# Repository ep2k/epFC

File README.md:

# epFC - Famicom Emulator on an FPGA

epFC is an implementation of Nintendo's __Family Computer__ (__Nintendo Entertainment System__) written in SystemVerilog.
It works on an FPGA board with a board for connection to Famicom cartridges.

It has no built-in mappers except for NROM, and can basically only operate in real-time communication with cartridges.

The operation has been confirmed with Terasic DE0-CV Board.

")

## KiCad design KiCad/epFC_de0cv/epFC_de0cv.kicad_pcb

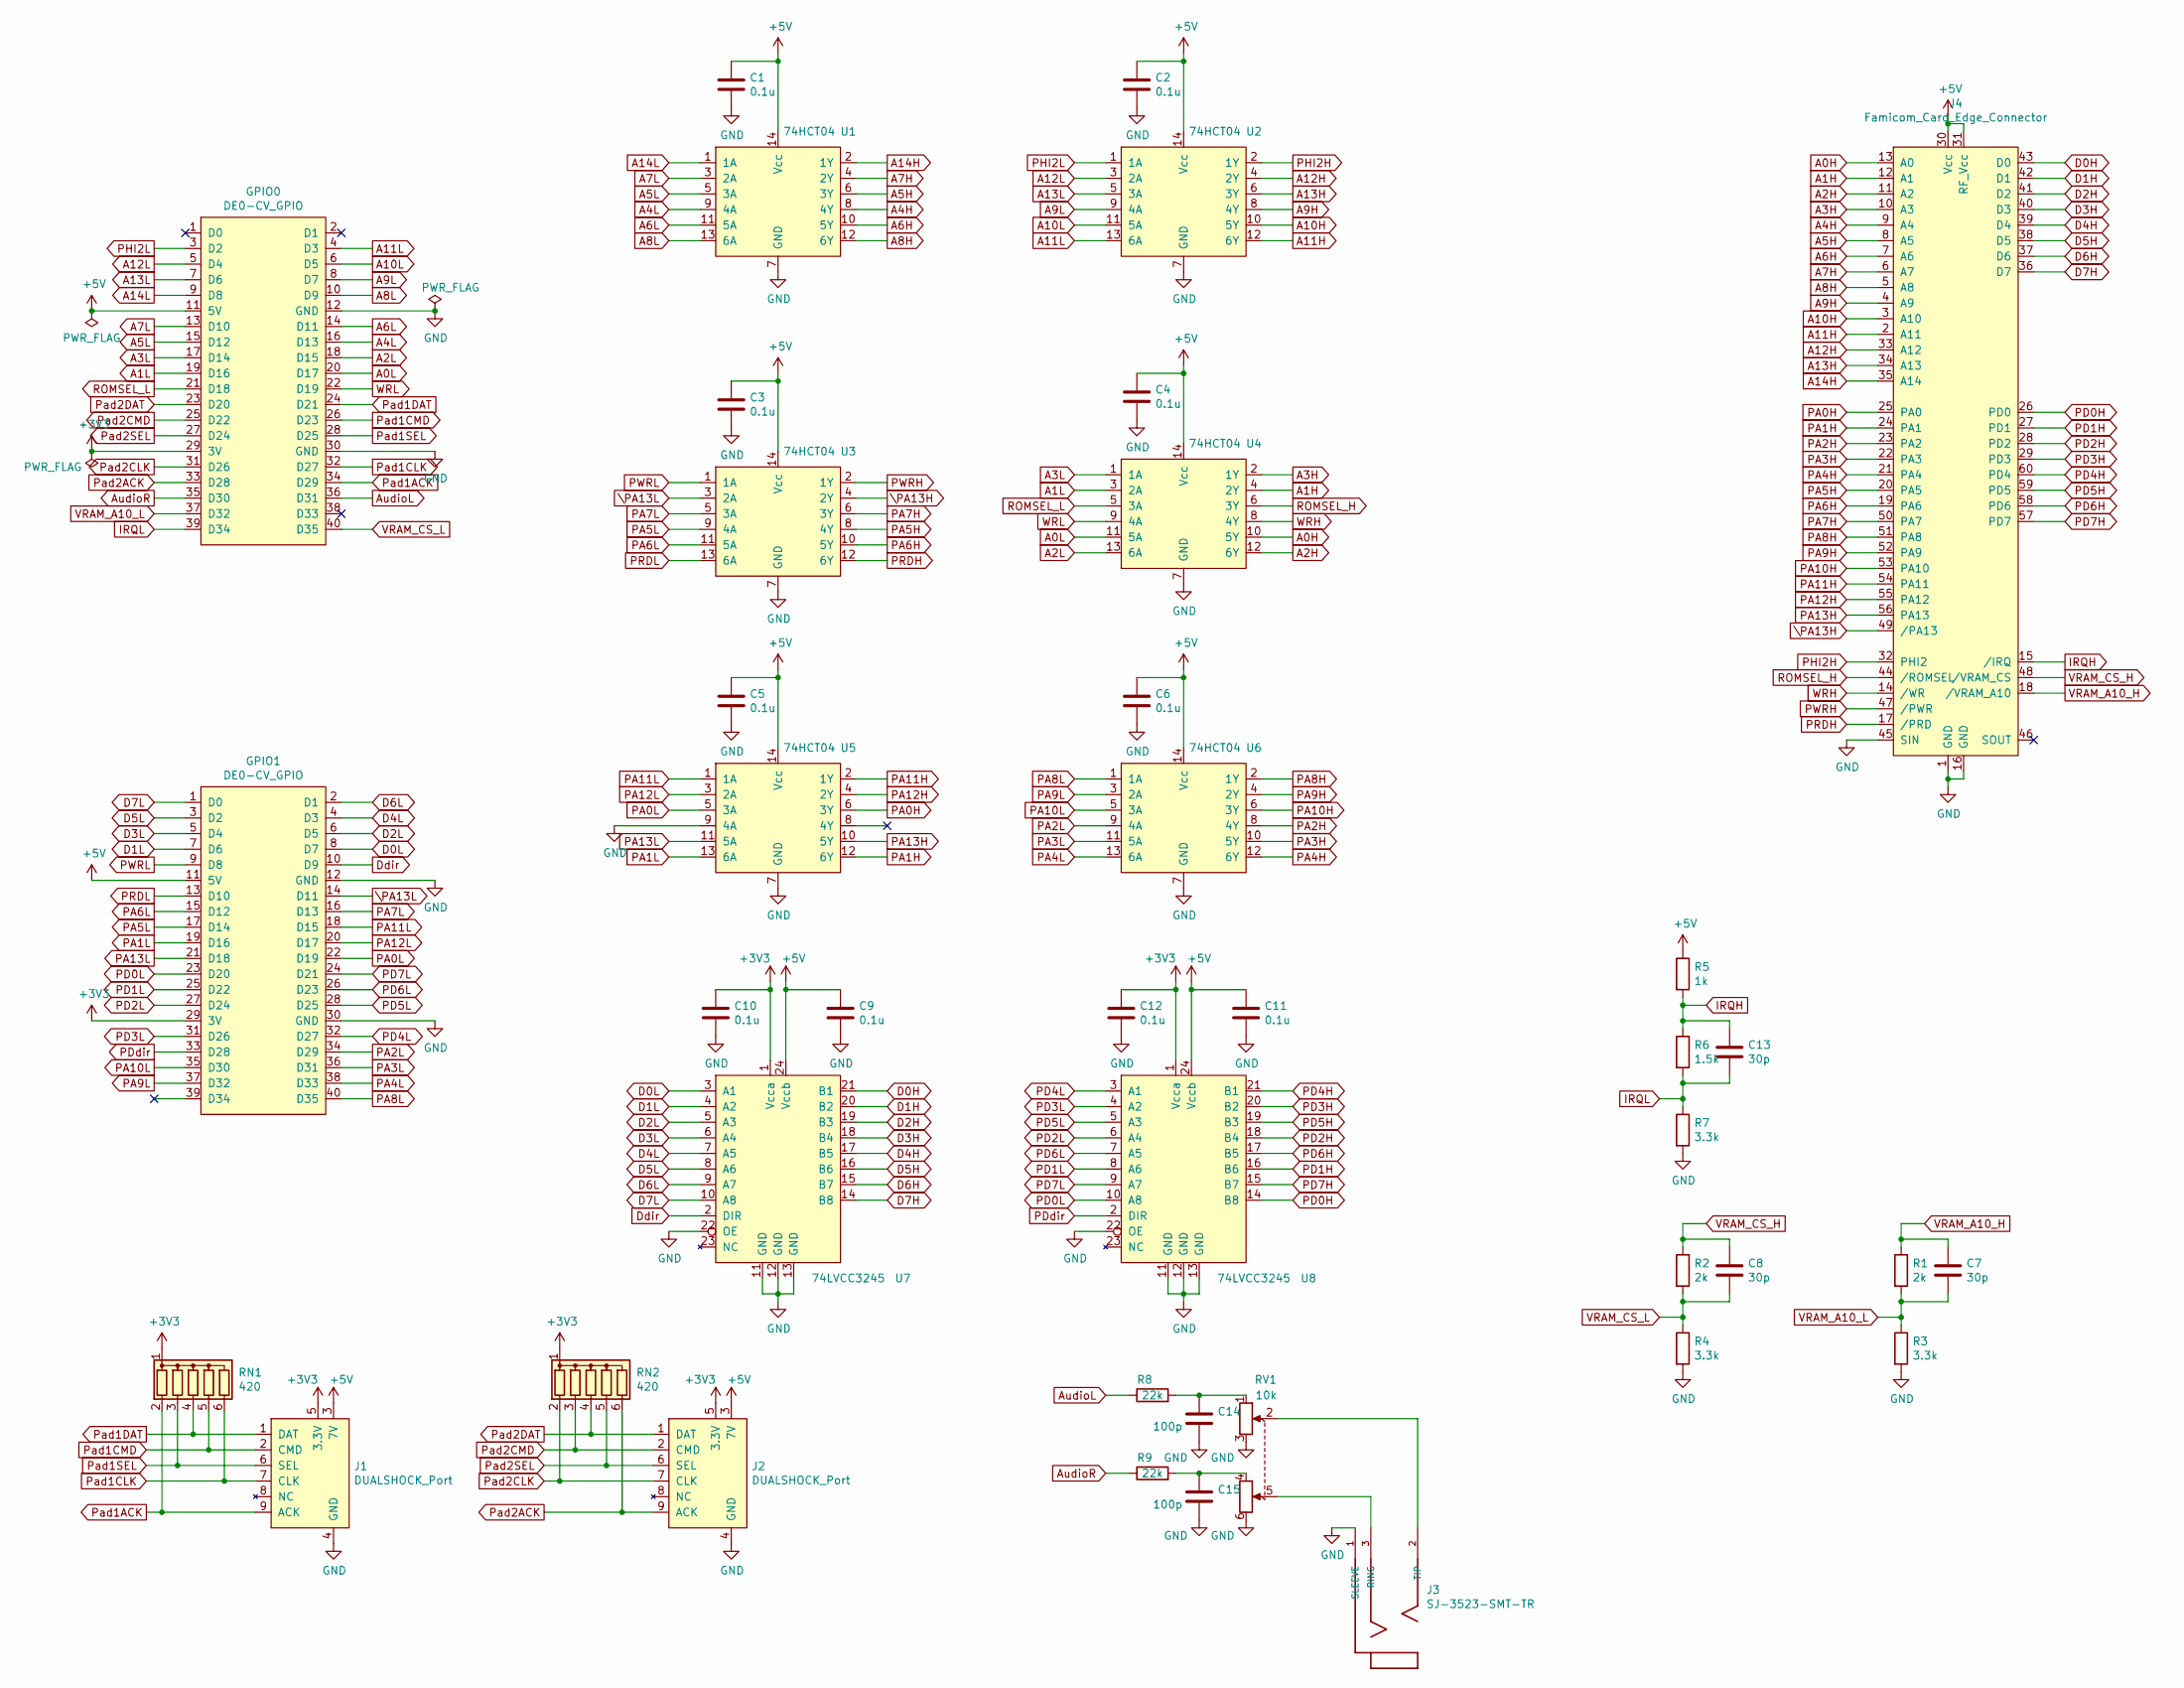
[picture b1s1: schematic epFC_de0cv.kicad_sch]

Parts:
C1, C2, C3, C4, C5, C6, C9, C10, C11, C12: 0.1u; C_1206_3216Metric_Pad1.33x1.80mm_HandSolder
C7, C8, C13: 30p; C_1206_3216Metric_Pad1.33x1.80mm_HandSolder
C14, C15: 100p; C_1206_3216Metric_Pad1.33x1.80mm_HandSolder
GPIO0, GPIO1: DE0-CV_GPIO; PinSocket_2x20_P2.54mm_Vertical_Back
J1, J2: DUALSHOCK_Port
J3: SJ-3523-SMT-TR; CUI_SJ-3523-SMT-TR
J4: Famicom_Card_Edge_Connector
R1, R2: 2k; R_1206_3216Metric_Pad1.30x1.75mm_HandSolder
R3, R4, R7: 3.3k; R_1206_3216Metric_Pad1.30x1.75mm_HandSolder
R5: 1k; R_1206_3216Metric_Pad1.30x1.75mm_HandSolder
R6: 1.5k; R_1206_3216Metric_Pad1.30x1.75mm_HandSolder
R8, R9: 22k; R_1206_3216Metric_Pad1.30x1.75mm_HandSolder
RN1, RN2: 420; R_Array_SIP6
RV1: 10k; Potentiometer_Bourns_PTV112
U1, U2, U3, U4, U5, U6: 74HCT04; SOIC-14_3.9x8.7mm_P1.27mm
U7, U8: 74LVCC3245; SO-24_5.3x15mm_P1.27mm

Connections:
+3V3: C10.1, C12.1, GPIO0.29 (3V), GPIO1.29 (3V), J1.5 (3.3V), J2.5 (3.3V), RN1.1 (common), RN2.1 (common), U7.1 (Vcca), U8.1 (Vcca)
+5V: C1.1, C2.1, C3.1, C4.1, C5.1, C6.1, C9.1, C11.1, GPIO0.11 (5V), GPIO1.11 (5V), J1.3 (7V), J2.3 (7V), J4.30 (Vcc), J4.31 (RF_Vcc), R5.1, U1.14 (Vcc), U2.14 (Vcc), U3.14 (Vcc), U4.14 (Vcc), U5.14 (Vcc), U6.14 (Vcc), U7.24 (Vccb), U8.24 (Vccb)
A0H: J4.13 (A0), U4.10 (5Y)
A0L: GPIO0.20 (D17), U4.11 (5A)
A1H: J4.12 (A1), U4.4 (2Y)
A1L: GPIO0.19 (D16), U4.3 (2A)
A2H: J4.11 (A2), U4.12 (6Y)
A2L: GPIO0.18 (D15), U4.13 (6A)
A3H: J4.10 (A3), U4.2 (1Y)
A3L: GPIO0.17 (D14), U4.1 (1A)
A4H: J4.9 (A4), U1.8 (4Y)
A4L: GPIO0.16 (D13), U1.9 (4A)
A5H: J4.8 (A5), U1.6 (3Y)
A5L: GPIO0.15 (D12), U1.5 (3A)
A6H: J4.7 (A6), U1.10 (5Y)
A6L: GPIO0.14 (D11), U1.11 (5A)
A7H: J4.6 (A7), U1.4 (2Y)
A7L: GPIO0.13 (D10), U1.3 (2A)
A8H: J4.5 (A8), U1.12 (6Y)
A8L: GPIO0.10 (D9), U1.13 (6A)
A9H: J4.4 (A9), U2.8 (4Y)
A9L: GPIO0.8 (D7), U2.9 (4A)
A10H: J4.3 (A10), U2.10 (5Y)
A10L: GPIO0.6 (D5), U2.11 (5A)
A11H: J4.2 (A11), U2.12 (6Y)
A11L: GPIO0.4 (D3), U2.13 (6A)
A12H: J4.33 (A12), U2.4 (2Y)
A12L: GPIO0.5 (D4), U2.3 (2A)
A13H: J4.34 (A13), U2.6 (3Y)
A13L: GPIO0.7 (D6), U2.5 (3A)
A14H: J4.35 (A14), U1.2 (1Y)
A14L: GPIO0.9 (D8), U1.1 (1A)
AudioL: GPIO0.36 (D31), R8.1
AudioR: GPIO0.35 (D30), R9.1
D0H: J4.43 (D0), U7.21 (B1)
D0L: GPIO1.8 (D7), U7.3 (A1)
D1H: J4.42 (D1), U7.20 (B2)
D1L: GPIO1.7 (D6), U7.4 (A2)
D2H: J4.41 (D2), U7.19 (B3)
D2L: GPIO1.6 (D5), U7.5 (A3)
D3H: J4.40 (D3), U7.18 (B4)
D3L: GPIO1.5 (D4), U7.6 (A4)
D4H: J4.39 (D4), U7.17 (B5)
D4L: GPIO1.4 (D3), U7.7 (A5)
D5H: J4.38 (D5), U7.16 (B6)
D5L: GPIO1.3 (D2), U7.8 (A6)
D6H: J4.37 (D6), U7.15 (B7)
D6L: GPIO1.2 (D1), U7.9 (A7)
D7H: J4.36 (D7), U7.14 (B8)
D7L: GPIO1.1 (D0), U7.10 (A8)
Ddir: GPIO1.10 (D9), U7.2 (DIR)
GND: C1.2, C2.2, C3.2, C4.2, C5.2, C6.2, C9.2, C10.2, C11.2, C12.2, C14.2, C15.2, GPIO0.12 (GND), GPIO0.30 (GND), GPIO1.12 (GND), GPIO1.30 (GND), J1.4 (GND), J2.4 (GND), J3.1 (SLEEVE), J4.1 (GND), J4.16 (GND), J4.45 (SIN), R3.2, R4.2, R7.2, RV1.3, RV1.6, U1.7 (GND), U2.7 (GND), U3.7 (GND), U4.7 (GND), U5.7 (GND), U5.9 (4A), U6.7 (GND), U7.11 (GND), U7.12 (GND), U7.13 (GND), U7.22 (OE), U8.11 (GND), U8.12 (GND), U8.13 (GND), U8.22 (OE)
IRQH: C13.1, J4.15 (/IRQ), R5.2, R6.1
IRQL: C13.2, GPIO0.39 (D34), R6.2, R7.1
unnamed: C14.1, R8.2, RV1.1
unnamed: C15.1, R9.2, RV1.4
unnamed: J3.3 (RING), RV1.5
unnamed: J3.2 (TIP), RV1.2
PA0H: J4.25 (PA0), U5.6 (3Y)
PA0L: GPIO1.22 (D19), U5.5 (3A)
PA1H: J4.24 (PA1), U5.12 (6Y)
PA1L: GPIO1.19 (D16), U5.13 (6A)
PA2H: J4.23 (PA2), U6.8 (4Y)
PA2L: GPIO1.34 (D29), U6.9 (4A)
PA3H: J4.22 (PA3), U6.10 (5Y)
PA3L: GPIO1.36 (D31), U6.11 (5A)
PA4H: J4.21 (PA4), U6.12 (6Y)
PA4L: GPIO1.38 (D33), U6.13 (6A)
PA5H: J4.20 (PA5), U3.8 (4Y)
PA5L: GPIO1.17 (D14), U3.9 (4A)
PA6H: J4.19 (PA6), U3.10 (5Y)
PA6L: GPIO1.15 (D12), U3.11 (5A)
PA7H: J4.50 (PA7), U3.6 (3Y)
PA7L: GPIO1.16 (D13), U3.5 (3A)
PA8H: J4.51 (PA8), U6.2 (1Y)
PA8L: GPIO1.40 (D35), U6.1 (1A)
PA9H: J4.52 (PA9), U6.4 (2Y)
PA9L: GPIO1.37 (D32), U6.3 (2A)
PA10H: J4.53 (PA10), U6.6 (3Y)
PA10L: GPIO1.35 (D30), U6.5 (3A)
PA11H: J4.54 (PA11), U5.2 (1Y)
PA11L: GPIO1.18 (D15), U5.1 (1A)
PA12H: J4.55 (PA12), U5.4 (2Y)
PA12L: GPIO1.20 (D17), U5.3 (2A)
PA13H: J4.56 (PA13), U5.10 (5Y)
PA13L: GPIO1.21 (D18), U5.11 (5A)
PD0H: J4.26 (PD0), U8.14 (B8)
PD0L: GPIO1.23 (D20), U8.10 (A8)
PD1H: J4.27 (PD1), U8.16 (B6)
PD1L: GPIO1.25 (D22), U8.8 (A6)
PD2H: J4.28 (PD2), U8.18 (B4)
PD2L: GPIO1.27 (D24), U8.6 (A4)
PD3H: J4.29 (PD3), U8.20 (B2)
PD3L: GPIO1.31 (D26), U8.4 (A2)
PD4H: J4.60 (PD4), U8.21 (B1)
PD4L: GPIO1.32 (D27), U8.3 (A1)
PD5H: J4.59 (PD5), U8.19 (B3)
PD5L: GPIO1.28 (D25), U8.5 (A3)
PD6H: J4.58 (PD6), U8.17 (B5)
PD6L: GPIO1.26 (D23), U8.7 (A5)
PD7H: J4.57 (PD7), U8.15 (B7)
PD7L: GPIO1.24 (D21), U8.9 (A7)
PDdir: GPIO1.33 (D28), U8.2 (DIR)
PHI2H: J4.32 (PHI2), U2.2 (1Y)
PHI2L: GPIO0.3 (D2), U2.1 (1A)
PRDH: J4.17 (/PRD), U3.12 (6Y)
PRDL: GPIO1.13 (D10), U3.13 (6A)
PWRH: J4.47 (/PWR), U3.2 (1Y)
PWRL: GPIO1.9 (D8), U3.1 (1A)
Pad1ACK: GPIO0.34 (D29), J1.9 (ACK), RN1.2 (R1)
Pad1CLK: GPIO0.32 (D27), J1.7 (CLK), RN1.6 (R5)
Pad1CMD: GPIO0.26 (D23), J1.2 (CMD), RN1.5 (R4)
Pad1DAT: GPIO0.24 (D21), J1.1 (DAT), RN1.4 (R3)
Pad1SEL: GPIO0.28 (D25), J1.6 (SEL), RN1.3 (R2)
Pad2ACK: GPIO0.33 (D28), J2.9 (ACK), RN2.6 (R5)
Pad2CLK: GPIO0.31 (D26), J2.7 (CLK), RN2.2 (R1)
Pad2CMD: GPIO0.25 (D22), J2.2 (CMD), RN2.3 (R2)
Pad2DAT: GPIO0.23 (D20), J2.1 (DAT), RN2.4 (R3)
Pad2SEL: GPIO0.27 (D24), J2.6 (SEL), RN2.5 (R4)
ROMSEL_H: J4.44 (/ROMSEL), U4.6 (3Y)
ROMSEL_L: GPIO0.21 (D18), U4.5 (3A)
VRAM_A10_H: C7.1, J4.18 (/VRAM_A10), R1.1
VRAM_A10_L: C7.2, GPIO0.37 (D32), R1.2, R3.1
VRAM_CS_H: C8.1, J4.48 (/VRAM_CS), R2.1
VRAM_CS_L: C8.2, GPIO0.40 (D35), R2.2, R4.1
WRH: J4.14 (/WR), U4.8 (4Y)
WRL: GPIO0.22 (D19), U4.9 (4A)
\PA13H: J4.49 (/PA13), U3.4 (2Y)
\PA13L: GPIO1.14 (D11), U3.3 (2A)

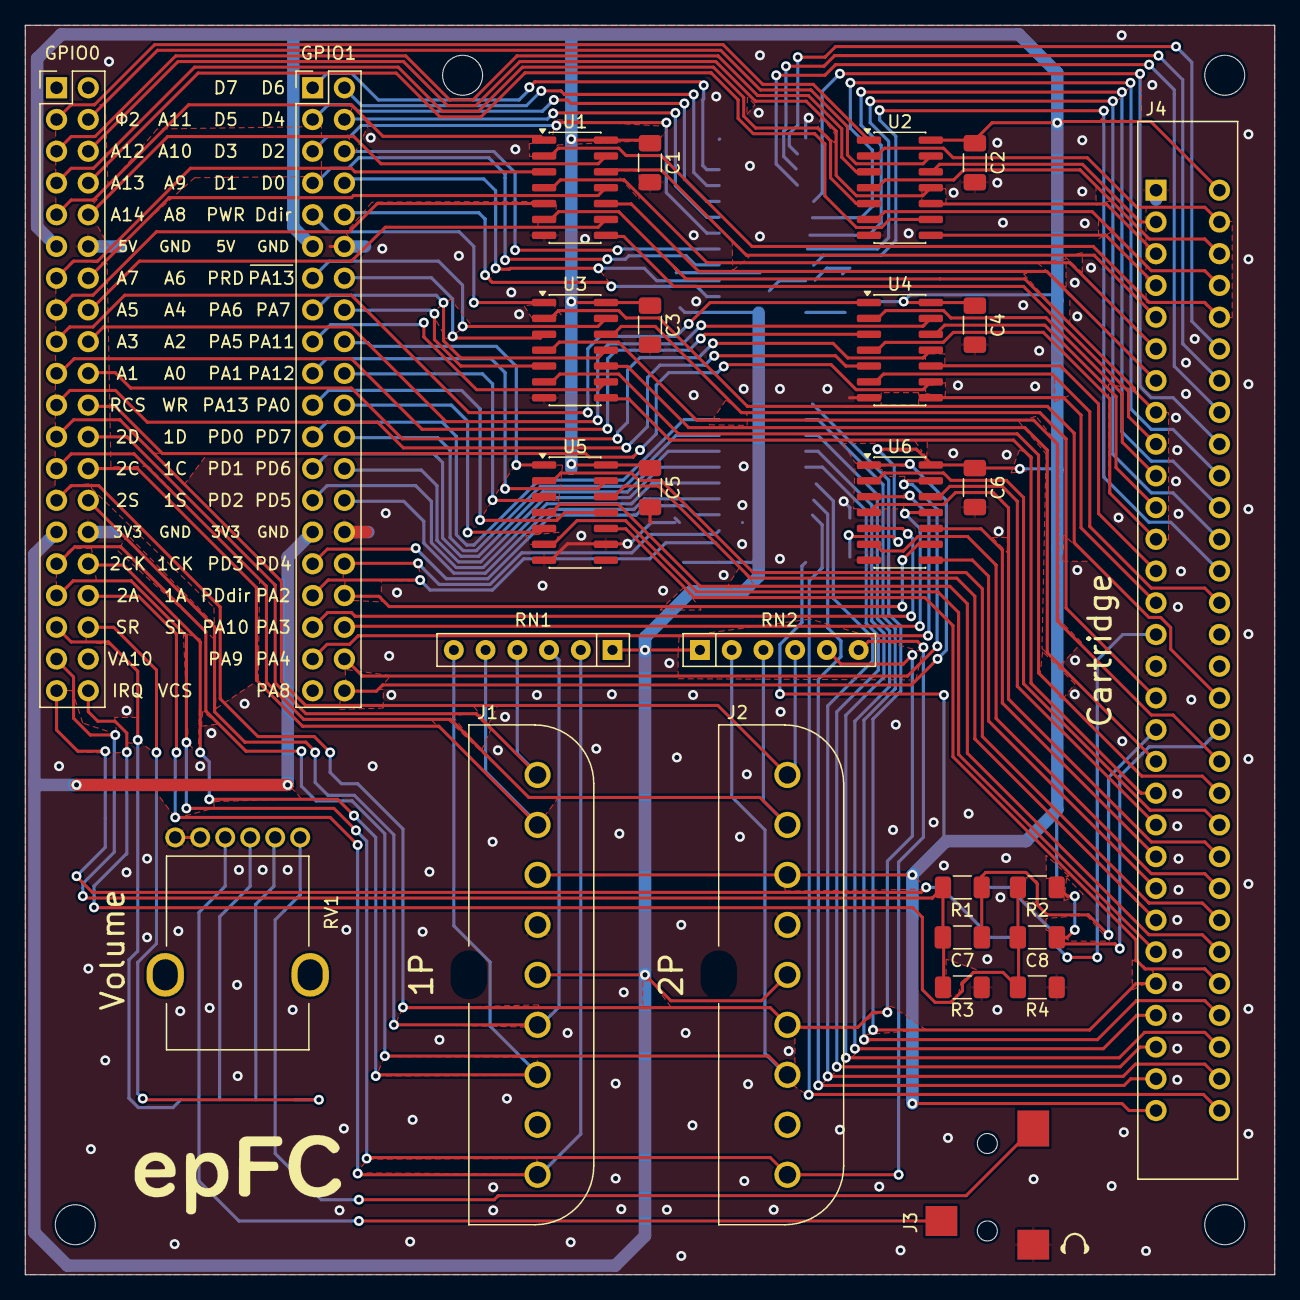
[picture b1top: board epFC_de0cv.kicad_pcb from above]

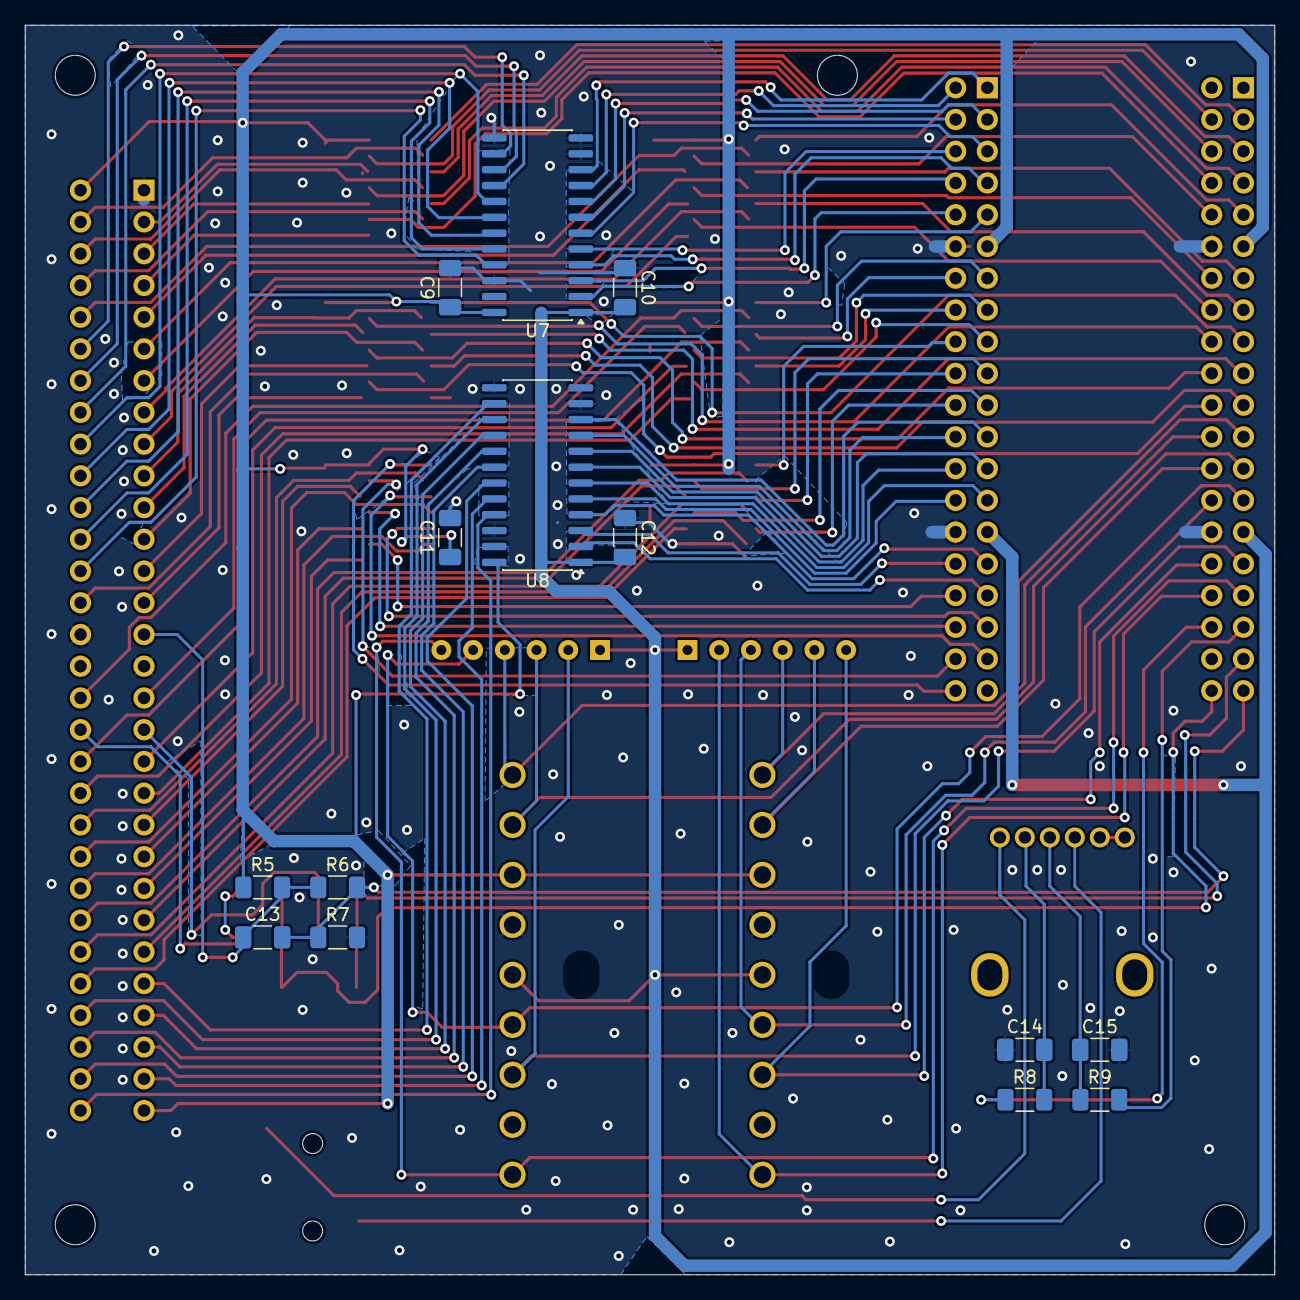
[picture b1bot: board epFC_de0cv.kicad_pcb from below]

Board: 2 copper layers, 100.0 x 100.0 mm, 41 parts (14 on the bottom side), 129 nets.

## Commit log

2023-01-13 add README.md
2023-01-13 Create LICENSE
2025-11-02 feat: #4 .gitignoreを追加
2025-11-02 feat: #4 カートリッジ接続基板のKiCadデータを追加
